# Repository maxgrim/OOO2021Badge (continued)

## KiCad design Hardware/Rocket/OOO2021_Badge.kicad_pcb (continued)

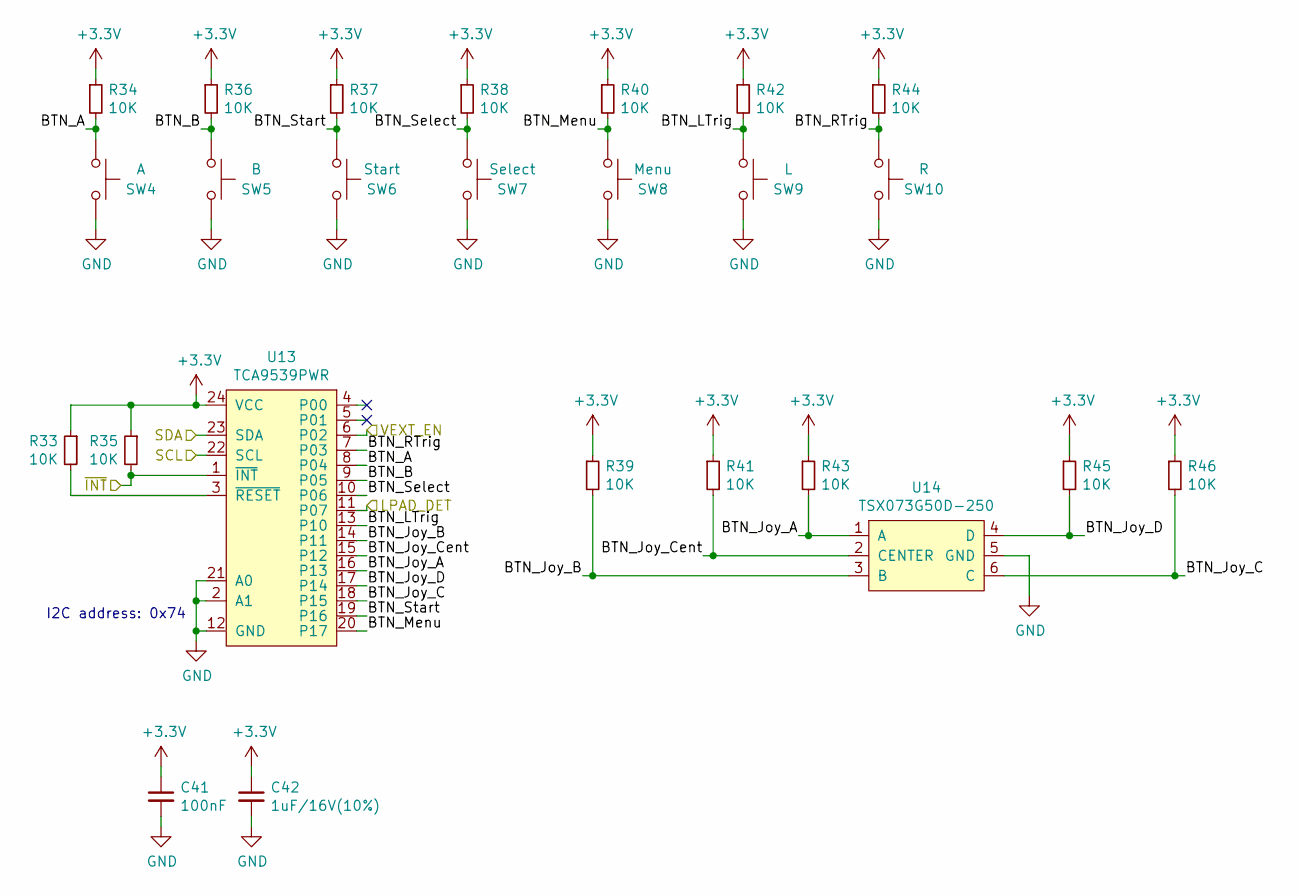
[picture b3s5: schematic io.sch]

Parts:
C41: 100nF; C_0402_1005Metric; LCSC C1581
C42: 1uF/16V(10%); C_0402_1005Metric; LCSC C29266
R33, R34, R35, R36, R37, R38, R39, R40, R41, R42, R43, R44, R45, R46: 10K; R_0402_1005Metric; LCSC C25744
SW4: A; SW-SMD_4P-L5.1-W5.1-P3.70-LS6.5-TL-2; LCSC C318887
SW5: B; SW-SMD_4P-L5.1-W5.1-P3.70-LS6.5-TL-2; LCSC C318887
SW6: Start; SW-SMD_4P-L5.1-W5.1-P3.70-LS6.5-TL-2; LCSC C318887
SW7: Select; SW-SMD_4P-L5.1-W5.1-P3.70-LS6.5-TL-2; LCSC C318887
SW8: Menu; SW-SMD_4P-L5.1-W5.1-P3.70-LS6.5-TL-2; LCSC C318887
SW9: L; KEY-TH_4P-L7.5-W6.8-P4.50-LS7.2; LCSC C455134
SW10: R; KEY-TH_4P-L7.5-W6.8-P4.50-LS7.2; LCSC C455134
U13: TCA9539PWR; TSSOP-24_4.4x7.8mm_P0.65mm; LCSC C131972
U14: TSX073G50D-250; SW-SMD_TSX073G50D1-250; LCSC C722953

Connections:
+3V3: C41.1, C42.1, R33.1, R34.1, R35.1, R36.1, R37.1, R38.1, R39.1, R40.1, R41.1, R42.1, R43.1, R44.1, R45.1, R46.1, U13.24 (VCC); also elsewhere on the board
/I2C_SCL: U13.22 (SCL); also elsewhere on the board
/I2C_SDA: U13.23 (SDA); also elsewhere on the board
/LPAD_DET: U13.11 (P07); also elsewhere on the board
/io/BTN_A: R34.2, SW4.1, U13.8 (P04)
/io/BTN_B: R36.2, SW5.1, U13.9 (P05)
/io/BTN_Joy_A: R43.2, U13.16 (P13), U14.1 (A)
/io/BTN_Joy_B: R39.2, U13.14 (P11), U14.3 (B)
/io/BTN_Joy_C: R46.2, U13.18 (P15), U14.6 (C)
/io/BTN_Joy_Cent: R41.2, U13.15 (P12), U14.2 (CENTER)
/io/BTN_Joy_D: R45.2, U13.17 (P14), U14.4 (D)
/io/BTN_LTrig: R42.2, SW9.1, U13.13 (P10)
/io/BTN_Menu: R40.2, SW8.1, U13.20 (P17)
/io/BTN_RTrig: R44.2, SW10.1, U13.7 (P03)
/io/BTN_Select: R38.2, SW7.1, U13.10 (P06)
/io/BTN_Start: R37.2, SW6.1, U13.19 (P16)
/io/VEXT_EN: U13.6 (P02); also elsewhere on the board
/~IO_INT: R35.2, U13.1 (~INT); also elsewhere on the board
GND: C41.2, C42.2, SW4.2, SW5.2, SW6.2, SW7.2, SW8.2, SW9.2, SW10.2, U13.2 (A1), U13.12 (GND), U13.21 (A0), U14.5 (GND); also elsewhere on the board
unnamed: R33.2, U13.3 (~RESET)

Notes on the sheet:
I2C address: 0x74

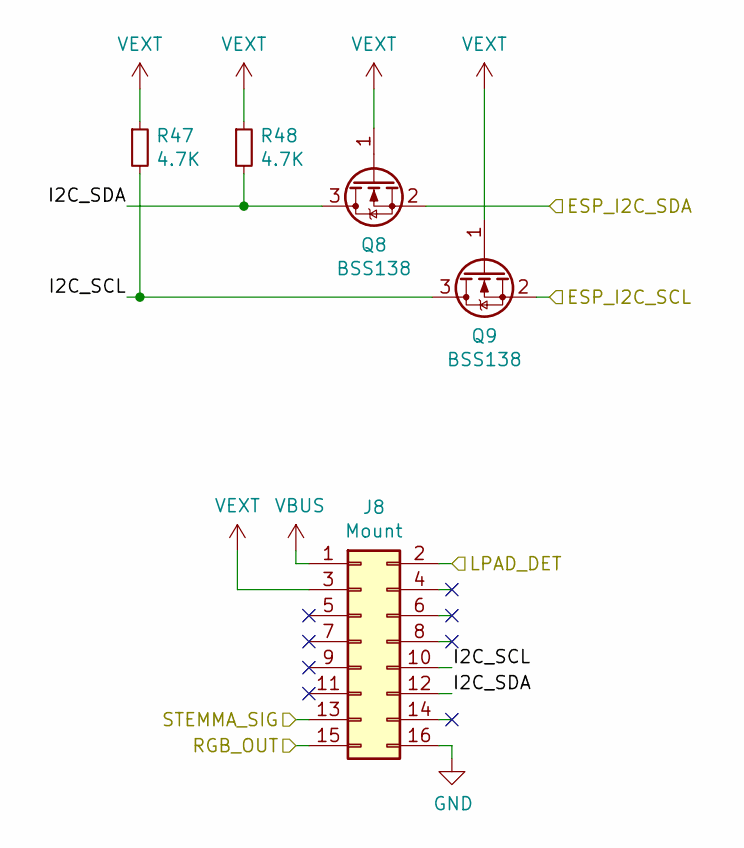
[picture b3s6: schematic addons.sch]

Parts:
J8: Mount; PinSocket_2x08_P2.54mm_Vertical; LCSC C30734
Q8, Q9: BSS138; SOT-23; LCSC C426569
R47, R48: 4.7K; R_0402_1005Metric; LCSC C25900

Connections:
/I2C_SCL: Q9.2 (S); also elsewhere on the board
/I2C_SDA: Q8.2 (S); also elsewhere on the board
/LPAD_DET: J8.2; also elsewhere on the board
/RGB_OUT: J8.15; also elsewhere on the board
/STEMMA_SIG: J8.13; also elsewhere on the board
/addons/I2C_SCL: J8.10, Q9.3 (D), R47.2
/addons/I2C_SDA: J8.12, Q8.3 (D), R48.2
GND: J8.16; also elsewhere on the board
VBUS: J8.1; also elsewhere on the board
VEXT: J8.3, Q8.1 (G), Q9.1 (G), R47.1, R48.1; also elsewhere on the board

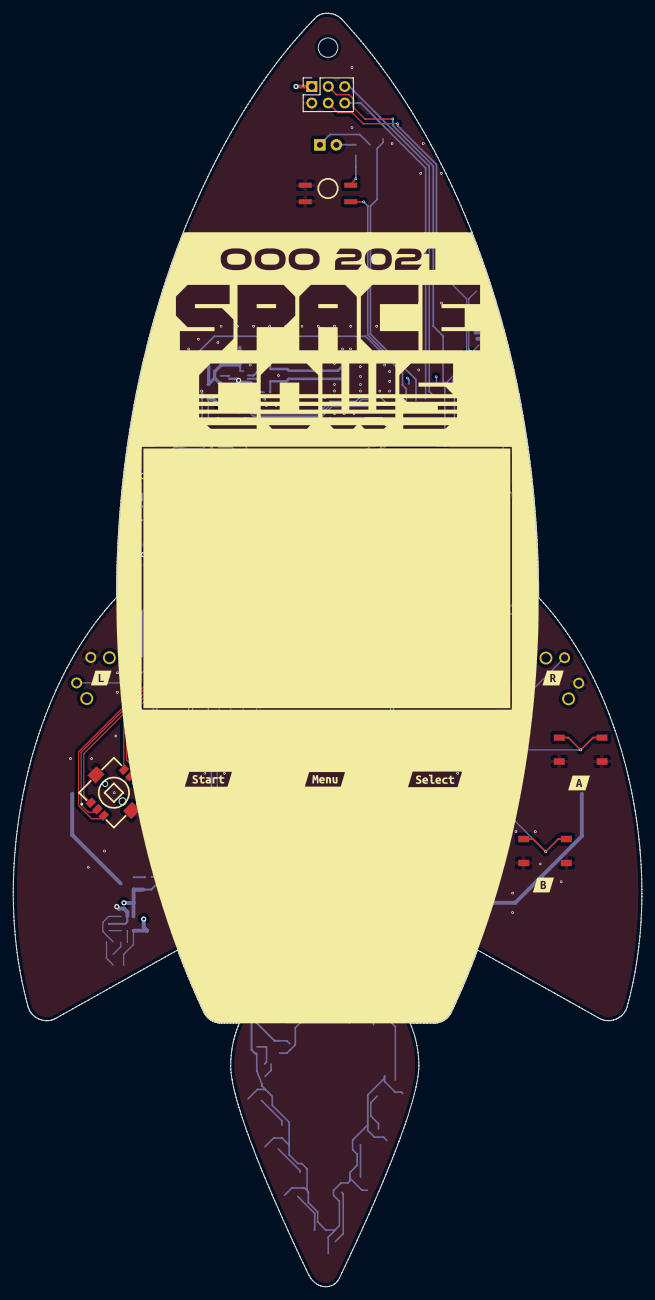
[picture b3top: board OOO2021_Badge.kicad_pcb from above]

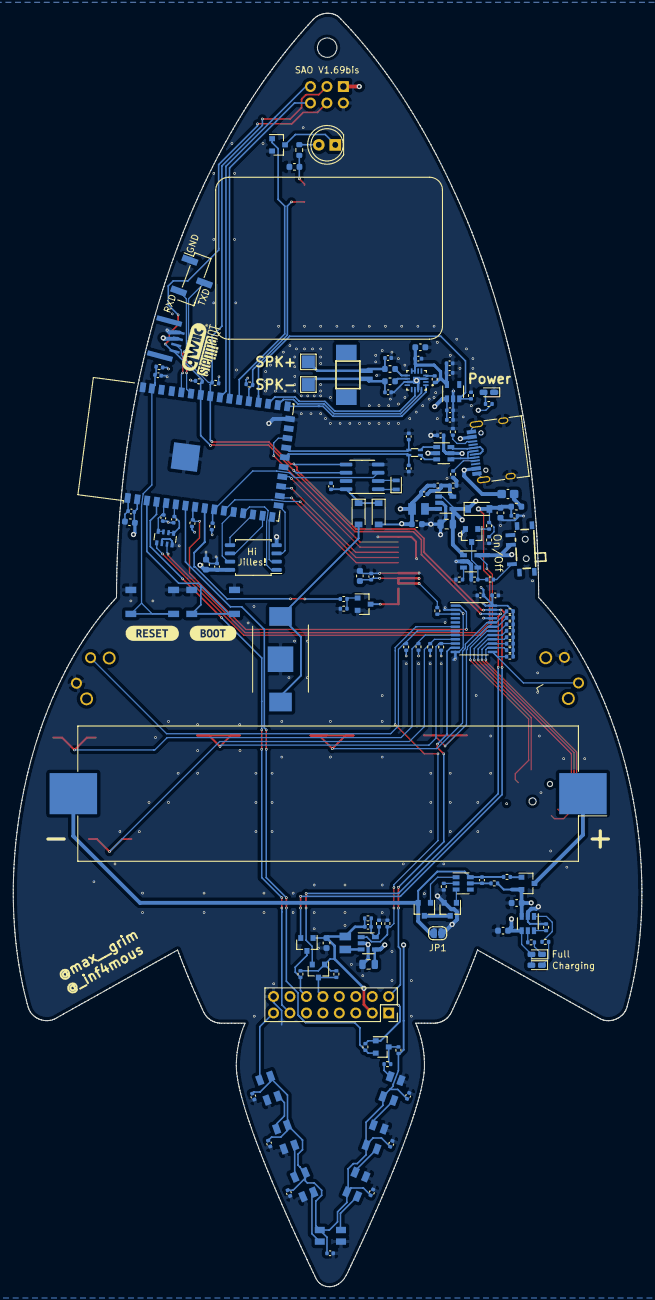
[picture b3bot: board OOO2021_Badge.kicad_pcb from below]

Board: 4 copper layers, 97.0 x 196.6 mm, 167 parts (152 on the bottom side), 110 nets.

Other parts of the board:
kibuzzard-612644FA, kibuzzard-612645F1, kibuzzard-6126412F, kibuzzard-6126450F, kibuzzard-6126461B, kibuzzard-61264142: G***; label

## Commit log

2021-10-18 Added .gitignore for KiCad projects
2021-10-18 Added hardware KiCad files
    Hardware files for Launchpad, Rocket (badge), and Moon addon
2021-10-18 Added example apps
2021-10-18 Ignore .DS_Store
2021-10-18 Added circuitpython submodule
2021-10-18 Attempt to re-add circuitpython
2021-10-18 Added circuitpython as submodule
2021-10-18 Added artwork and renders
2021-10-21 Created CowVSAlien game. Rotation to be fixed
2021-10-21 Added clock App
2021-10-21 Added Parrot App
2021-10-23 Added Intro / OLED
2021-10-23 Moved circuitpython to ooo_2021 branch
2021-10-23 Commit from james
2021-10-23 Battery Level App
2021-10-23 New menu
2021-10-25 Laser tag modifications
2021-10-26 Removed circuitpython
2021-10-26 Remove circuitpython
2021-10-26 Added circuitpython ooo2021_6
2021-10-26 Added new menu logic
2021-10-26 Updated menu
2021-10-26 Updated circuitpython
2021-10-26 Updated all apps to support return to menu and new IOexpander calls
2021-10-26 Point circuitpython to ooo2021_7
2021-10-26 Update menu and appstore
2021-10-26 Updated all apps to have a manifest for attribution or shame
2021-10-26 Finished Intro and modified clock app
2021-10-26 Added 8 bit cow on the rocket
2021-10-27 NeoPixel animation example app
2021-10-27 Added Cedrics name
2021-10-27 Whoami App
2021-10-27 Whoami app manifest.json
2021-10-27 About modified
2021-10-27 Added battery simbol for charging
2021-10-27 Remove submodule
2021-10-27 Updated appstore and code
2021-10-27 Added battery indicator
2021-10-27 Remove bs
2021-10-28 Moved apps
2021-10-28 Hide settings.py
2021-10-28 Added firmware update
2021-10-28 Fixed menu issues
2021-10-28 Improvements
2021-10-28 Fixes
2021-11-02 Renamed folders
2021-11-02 Fix menu back bug, added metadata.json reading
2021-11-02 Added comments for clarity
2021-11-02 Added Go Back to the apps menu
2021-11-02 Moved sync script
